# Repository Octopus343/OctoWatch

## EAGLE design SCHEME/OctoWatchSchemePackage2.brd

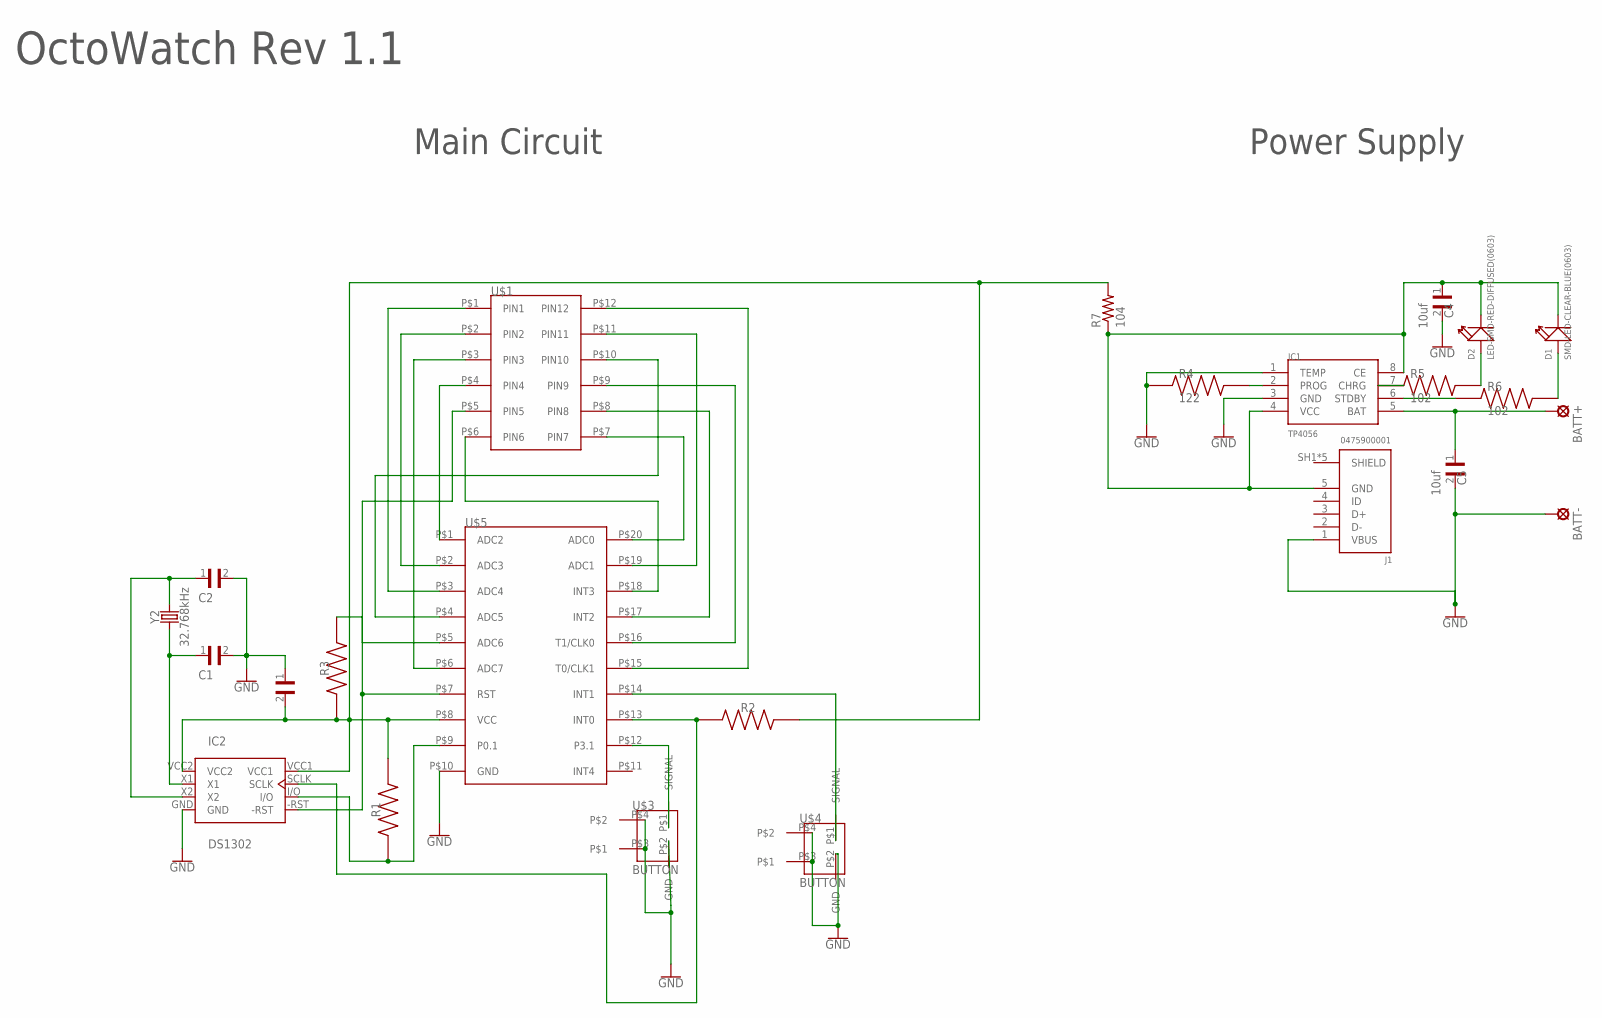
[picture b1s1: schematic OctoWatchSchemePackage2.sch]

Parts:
BATT+: LSP13
BATT-: LSP13
C1, C2: CL21C220JBANNNC; CAPC2012X140N
C3: CL21B104KCFNNNE; CAPC2012X140N
C4, C5: 10uf; CAPC1608X100N
D1: SMD-LED-CLEAR-BLUE(0603); LED-0603
D2: LED-SMD-RED-DIFFUSED(0603); LED-0603
IC1: TP4056; SOP-8
IC2: DS1302; DIL08
J1: 0475900001
R1, R2, R3: ERA3AEB103V; RES_ERA3AEB103V
R4: 122; RESC3116X65N
R5, R6: 102; RESC1608X55N
R7: 104; R0805
U$1: LED_SEGMENT
U$3, U$4: BUTTON
U$5: STC15F204AE
Y2: 32.768kHz; CRYSTAL-PTH-2X6-CYL

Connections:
BATT+: C3.2, IC2.VCC1, IC2.VCC2, R1.2, R2.2, R3.1, R7.2, U$5.P$8 (VCC)
GND: BATT-.MP, C1.2, C2.2, C3.1, C4.2, C5.2, IC1.1 (TEMP), IC1.3 (GND), IC2.GND, J1.1 (VBUS), R4.1, U$3.P$2 (GND), U$3.P$3, U$3.P$4, U$4.P$2 (GND), U$4.P$3, U$4.P$4, U$5.P$10 (GND)
unnamed: U$1.P$1 (PIN1), U$5.P$3 (ADC4)
unnamed: U$1.P$2 (PIN2), U$5.P$2 (ADC3)
unnamed: U$1.P$4 (PIN4), U$5.P$1 (ADC2)
unnamed: U$1.P$3 (PIN3), U$5.P$6 (ADC7)
unnamed: U$1.P$5 (PIN5), U$5.P$5 (ADC6)
unnamed: U$1.P$6 (PIN6), U$5.P$18 (INT3)
unnamed: U$1.P$7 (PIN7), U$5.P$20 (ADC0)
unnamed: U$1.P$8 (PIN8), U$5.P$17 (INT2)
unnamed: U$1.P$9 (PIN9), U$5.P$16 (T1/CLK0)
unnamed: IC2.SCLK, R2.1, U$5.P$13 (INT0)
unnamed: IC2.-RST, R3.2, U$5.P$7 (RST)
unnamed: U$1.P$12 (PIN12), U$5.P$15 (T0/CLK1)
unnamed: C1.1, IC2.X1, Y2.1
unnamed: C4.1, D1.-, D2.-, IC1.4 (VCC), IC1.8 (CE), J1.5 (GND), R7.1
unnamed: C2.1, IC2.X2, Y2.2
unnamed: U$1.P$10 (PIN10), U$5.P$4 (ADC5)
unnamed: IC2.I/O, R1.1, U$5.P$9 (P0.1)
unnamed: BATT+.MP, C5.1, IC1.5 (BAT)
unnamed: U$4.P$1 (SIGNAL), U$5.P$14 (INT1)
unnamed: U$3.P$1 (SIGNAL), U$5.P$12 (P3.1)
unnamed: U$1.P$11 (PIN11), U$5.P$19 (ADC1)
unnamed: IC1.6 (STDBY), R6.1
unnamed: D1.+, R6.2
unnamed: IC1.7 (CHRG), R5.1
unnamed: D2.+, R5.2
unnamed: IC1.2 (PROG), R4.2
SHIELD: J1.SH1 (SHIELD), J1.SH2 (SHIELD), J1.SH3 (SHIELD), J1.SH4 (SHIELD), J1.SH5 (SHIELD)

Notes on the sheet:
OctoWatch Rev 1.1
Main Circuit
Power Supply

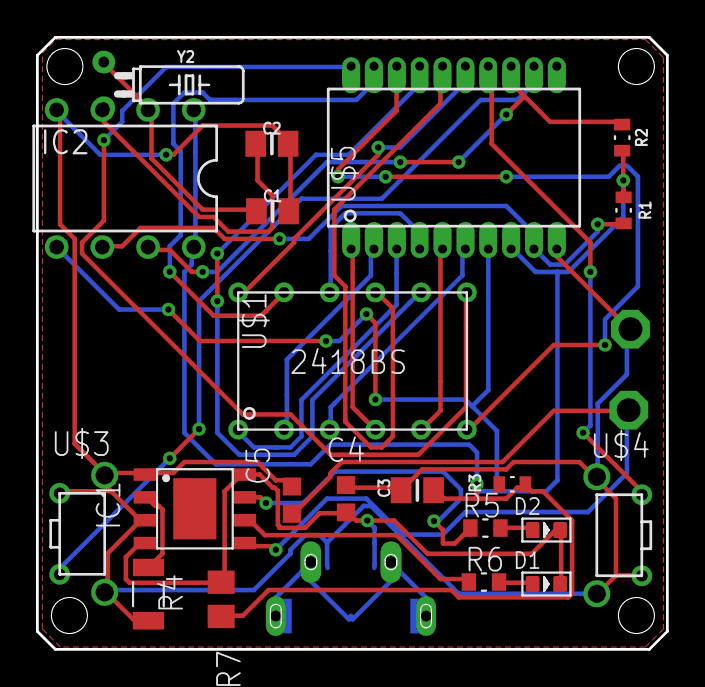
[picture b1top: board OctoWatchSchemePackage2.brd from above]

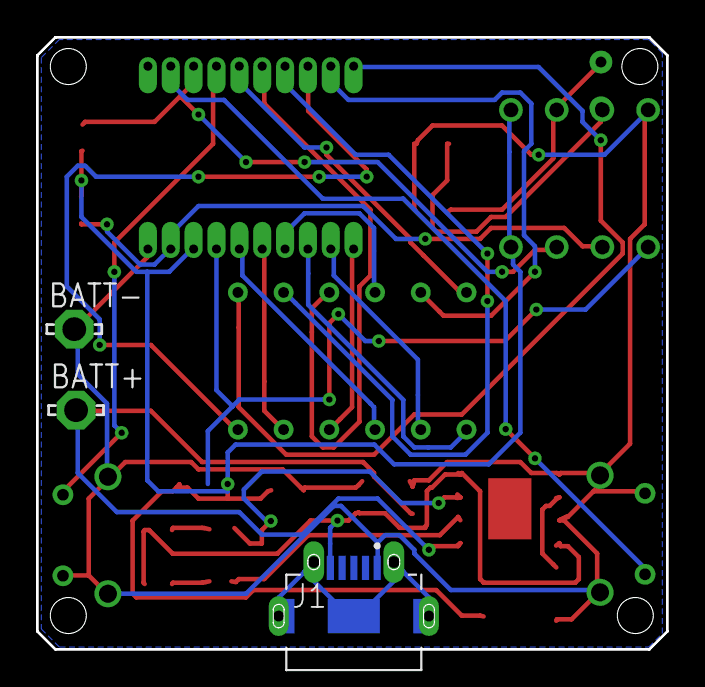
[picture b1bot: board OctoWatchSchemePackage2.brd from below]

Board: 2 copper layers, 35.0 x 34.0 mm, 24 parts (3 on the bottom side), 29 nets.

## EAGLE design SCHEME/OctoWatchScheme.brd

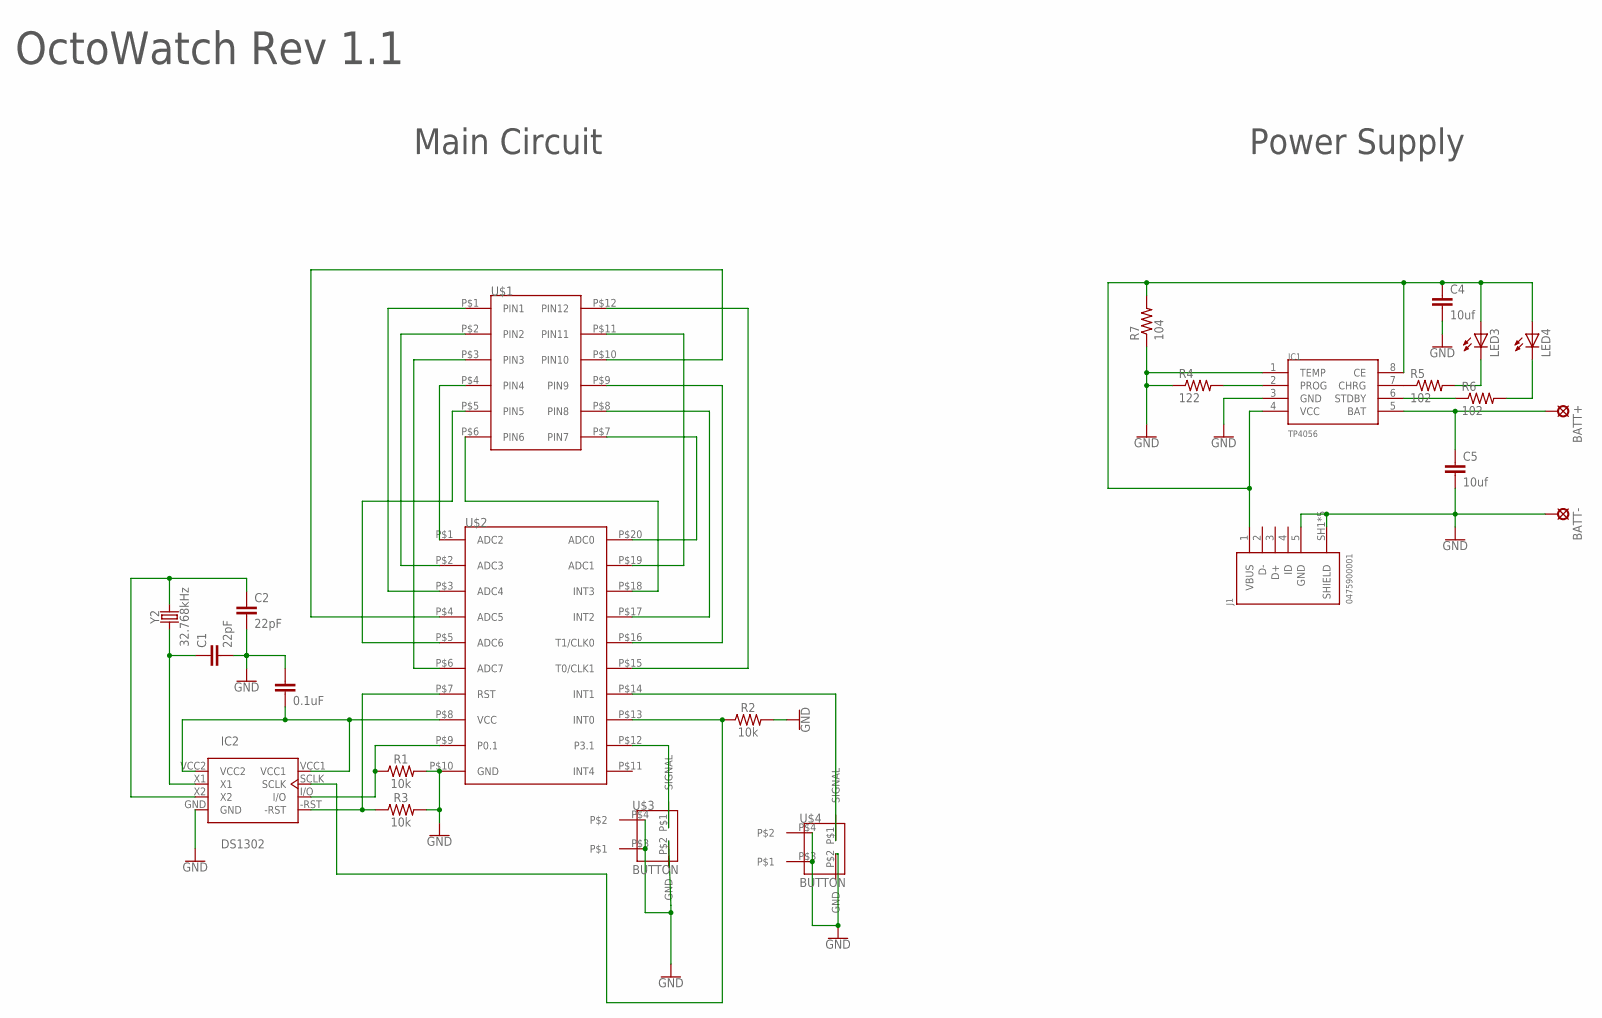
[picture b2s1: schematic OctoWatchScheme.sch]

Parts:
BATT+: LSP13
BATT-: LSP13
C1, C2: 22pF; 0402-TIGHT
C3: 0.1uF; 0402
C4, C5: 10uf; C0805
IC1: TP4056; SOP-8
IC2: DS1302; DIL08
J1: 0475900001
LED3, LED4: LEDCHIPLED_0603; CHIPLED_0603
R1, R2, R3: 10k; 0603
R4: 122; R0402
R5, R6: 102; R0402
R7: 104; R0805
U$1: LED_SEGMENT
U$2: STC15F204AESTC15L204AE; STC15F204AE2
U$3, U$4: BUTTON
Y2: 32.768kHz; CRYSTAL-PTH-2X6-CYL

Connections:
BATT+: C3.2, IC2.VCC1, IC2.VCC2, U$2.P$8 (VCC)
GND: BATT-.MP, C1.2, C2.2, C3.1, C4.2, C5.2, IC1.1 (TEMP), IC1.3 (GND), IC2.GND, J1.5 (GND), J1.SH1 (SHIELD), J1.SH2 (SHIELD), J1.SH3 (SHIELD), J1.SH4 (SHIELD), J1.SH5 (SHIELD), R1.2, R2.2, R3.2, R4.1, R7.1, U$2.P$10 (GND), U$3.P$2 (GND), U$3.P$3, U$3.P$4, U$4.P$2 (GND), U$4.P$3, U$4.P$4
unnamed: U$1.P$1 (PIN1), U$2.P$3 (ADC4)
unnamed: U$1.P$2 (PIN2), U$2.P$2 (ADC3)
unnamed: U$1.P$4 (PIN4), U$2.P$1 (ADC2)
unnamed: U$1.P$3 (PIN3), U$2.P$6 (ADC7)
unnamed: U$1.P$5 (PIN5), U$2.P$5 (ADC6)
unnamed: U$1.P$6 (PIN6), U$2.P$18 (INT3)
unnamed: U$1.P$7 (PIN7), U$2.P$20 (ADC0)
unnamed: U$1.P$8 (PIN8), U$2.P$17 (INT2)
unnamed: U$1.P$9 (PIN9), U$2.P$16 (T1/CLK0)
unnamed: U$1.P$10 (PIN10), U$2.P$4 (ADC5)
unnamed: U$1.P$11 (PIN11), U$2.P$19 (ADC1)
unnamed: U$1.P$12 (PIN12), U$2.P$15 (T0/CLK1)
unnamed: C1.1, IC2.X1, Y2.1
unnamed: IC2.-RST, R3.1, U$2.P$7 (RST)
unnamed: C2.1, IC2.X2, Y2.2
unnamed: IC2.I/O, R1.1, U$2.P$9 (P0.1)
unnamed: BATT+.MP, C5.1, IC1.5 (BAT)
unnamed: U$2.P$14 (INT1), U$4.P$1 (SIGNAL)
unnamed: U$2.P$12 (P3.1), U$3.P$1 (SIGNAL)
unnamed: IC2.SCLK, R2.1, U$2.P$13 (INT0)
unnamed: IC1.6 (STDBY), R6.1
unnamed: LED4.C, R6.2
unnamed: IC1.7 (CHRG), R5.1
unnamed: LED3.C, R5.2
unnamed: IC1.2 (PROG), R4.2
unnamed: C4.1, IC1.4 (VCC), IC1.8 (CE), J1.1 (VBUS), LED3.A, LED4.A, R7.2

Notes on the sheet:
OctoWatch Rev 1.1
Main Circuit
Power Supply

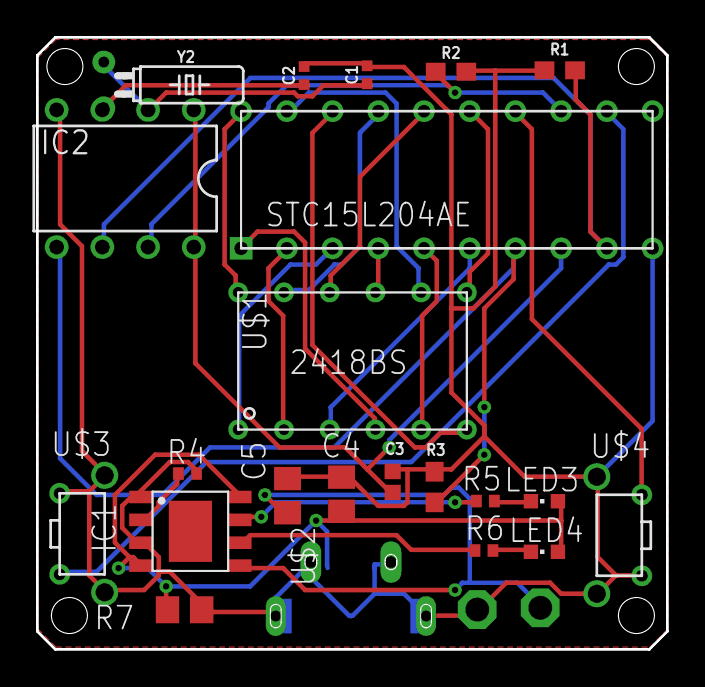
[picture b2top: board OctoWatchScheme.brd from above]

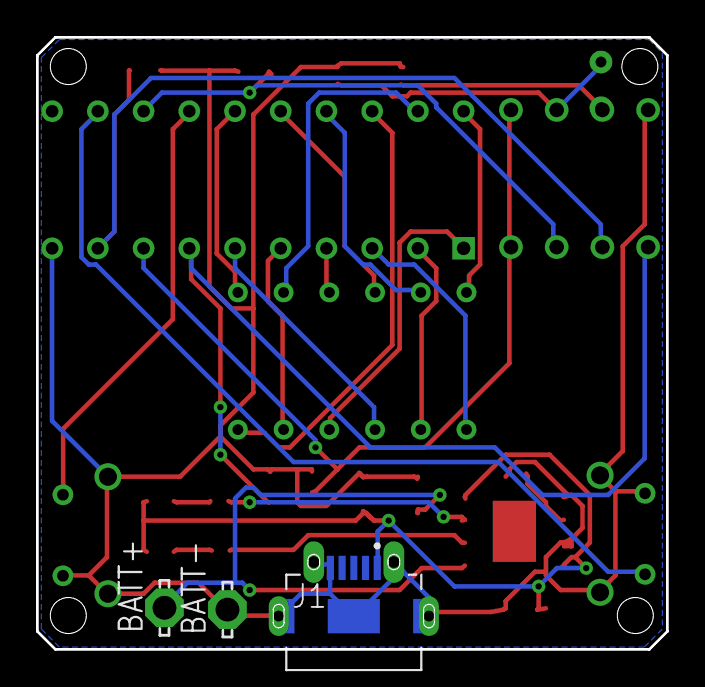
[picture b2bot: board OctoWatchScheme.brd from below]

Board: 2 copper layers, 35.0 x 34.0 mm, 24 parts (3 on the bottom side), 28 nets.

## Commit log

2021-01-08 Nixie Watch Project
2021-02-23 Pushing SchemeFile
2021-02-23 Pushing Scheme
2021-02-23 Updating...
2021-02-23 Reformating
2021-02-23 Finalazing scheme
2021-02-24 silking changed
2021-02-24 GerBer Added
2021-03-17 Add files via upload
    adding scheme pics
2021-03-18 working...
2021-03-22 adding 2nd ver
2021-04-13 Adding new package
2021-07-08 Sync
2021-07-11 Finalizing...

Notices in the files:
parts and their libraries:
SparkFun-Resistors: Licensing: Creative Commons ShareAlike 4.0 International - https://creativecommons.org/licenses/by-sa/4.0
